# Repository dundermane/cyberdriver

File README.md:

CyberDriver
===========

Driver for the Kopin Cyberdisplay 320m

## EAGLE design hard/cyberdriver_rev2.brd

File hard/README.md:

Hardware
=========

<h2>Eagle Version: <i>v6.5.0</i></h2>

<h3>all parts must be saved in the cyberdriver.lbr library</h3>
<h4>open cyberdriver.lbr and try [right-click -> Copy To Library] in the control panel</h4>
<h4><i>extra steps suck. but so does losing all of your work when a library changes</i></h4>

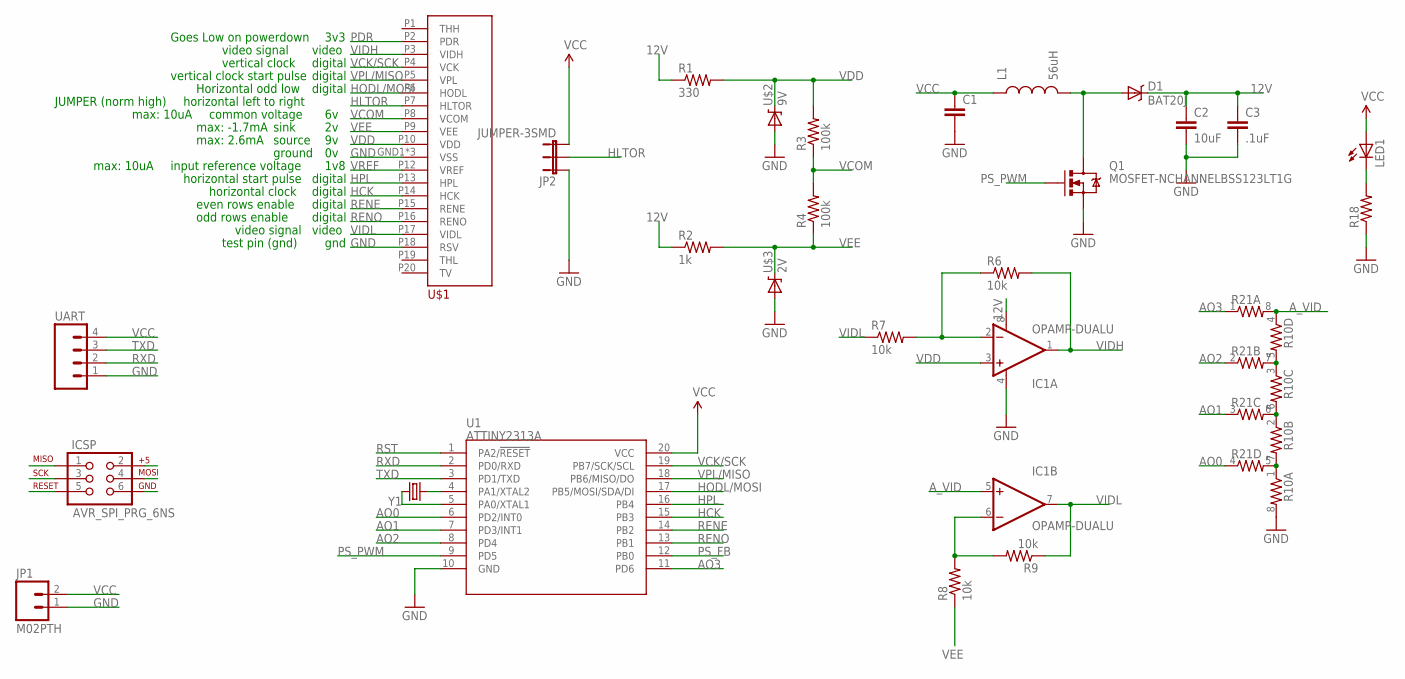
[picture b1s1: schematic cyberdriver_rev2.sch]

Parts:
C1: CAP1206; 1206
C2: 10uF; 1210
C3: .1uF; 0603-CAP
D1: BAT20J; SOD-323
IC1: OPAMP-DUALU; SO08
ICSP: AVR_SPI_PRG_6NS; 2X3-NS
JP1: M02PTH; 1X02
JP2: JUMPER-3SMD; SJ_3
L1: 56uH; SDR0403
LED1: LED1206; LED-1206
Q1: MOSFET-NCHANNELBSS123LT1G; SOT23
R1: 330; 0603-RES
R2: 1k; 0603-RES
R3, R4: 100k; 0603-RES
R6, R7, R8, R9: 10k; 0603-RES
R10, R21: RESISTOR-ARRAY0603-ARV; 0603-ARV
R18: RESISTOR0805-RES; 0805
U1: ATTINY2313A; SOP20W
U$1: CYBERDISPLAY-CONN; MOLEX-54550-2071
U$2: 9V; SOD-323
U$3: 2V; SOD-323
UART: M041.27MM; 1X04-1.27MM
Y1: CRYSTAL5X3; CRYSTAL-SMD-5X3

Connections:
12V: C2.1, C3.1, D1.C, IC1.8 (V+), R1.1, R2.1
AO0: R21.4 (1), U1.6 (PD2/INT0)
AO1: R21.3 (1), U1.7 (PD3/INT1)
AO2: R21.2 (1), U1.8 (PD4)
AO3: R21.1, U1.11 (PD6)
A_VID: IC1.5 (+IN), R10.4 (1), R21.8 (2)
GND: C1.2, C2.2, C3.2, IC1.4 (V-), ICSP.6, JP1.1, JP2.1, Q1.2 (S), R10.8 (2), R18.1, U1.10 (GND), U$1.GND1 (VSS), U$1.GND20 (VSS), U$1.P11 (VSS), U$1.P18 (RSV), U$2.A, U$3.A, UART.1
HCK: U1.15 (PB3), U$1.P14 (HCK)
HLTOR: JP2.2, U$1.P7 (HLTOR)
HODL/MOSI: ICSP.4, U1.17 (PB5/MOSI/SDA/DI), U$1.P6 (HODL)
HPL: U1.16 (PB4), U$1.P13 (HPL)
unnamed: U1.5 (PA0/XTAL1), Y1.3 (2)
unnamed: U1.4 (PA1/XTAL2), Y1.1
unnamed: LED1.C, R18.2
unnamed: D1.A, L1.P$2 (2), Q1.3 (D)
unnamed: IC1.2 (-IN), R6.1, R7.2
unnamed: R10.3 (1), R10.5 (2), R21.7 (2)
unnamed: IC1.6 (-IN), R8.2, R9.2
unnamed: R10.2 (1), R10.6 (2), R21.6 (2)
unnamed: R10.1, R10.7 (2), R21.5 (2)
PDR: U$1.P2 (PDR)
PS_FB: U1.12 (PB0)
PS_PWM: Q1.1 (G), U1.9 (PD5)
RENE: U1.14 (PB2), U$1.P15 (RENE)
RENO: U1.13 (PB1), U$1.P16 (RENO)
RST: ICSP.5, U1.1 (PA2/!RESET)
RXD: U1.2 (PD0/RXD), UART.2
TXD: U1.3 (PD1/TXD), UART.3
VCC: C1.1, ICSP.2, JP1.2, JP2.3, L1.P$1 (1), LED1.A, U1.20 (VCC), UART.4
VCK/SCK: ICSP.3, U1.19 (PB7/SCK/SCL), U$1.P4 (VCK)
VCOM: R3.1, R4.2, U$1.P8 (VCOM)
VDD: IC1.3 (+IN), R1.2, R3.2, U$1.P10 (VDD), U$2.C
VEE: R2.2, R4.1, R8.1, U$1.P9 (VEE), U$3.C
VIDH: IC1.1 (OUT), R6.2, U$1.P3 (VIDH)
VIDL: IC1.7 (OUT), R7.1, R9.1, U$1.P17 (VIDL)
VPL/MISO: ICSP.1, U1.18 (PB6/MISO/DO), U$1.P5 (VPL)
VREF: U$1.P12 (VREF)

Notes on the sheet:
Goes Low on powerdown
video signal
vertical clock
vertical clock start pulse
Horizontal odd low
horizontal left to right
common voltage
sink
source
ground
input reference voltage
horizontal start pulse
horizontal clock
even rows enable
odd rows enable
test pin (gnd)
digital
video
gnd
3v3
1v8
JUMPER (norm high)
max: 2.6mA
max: -1.7mA
max: 10uA

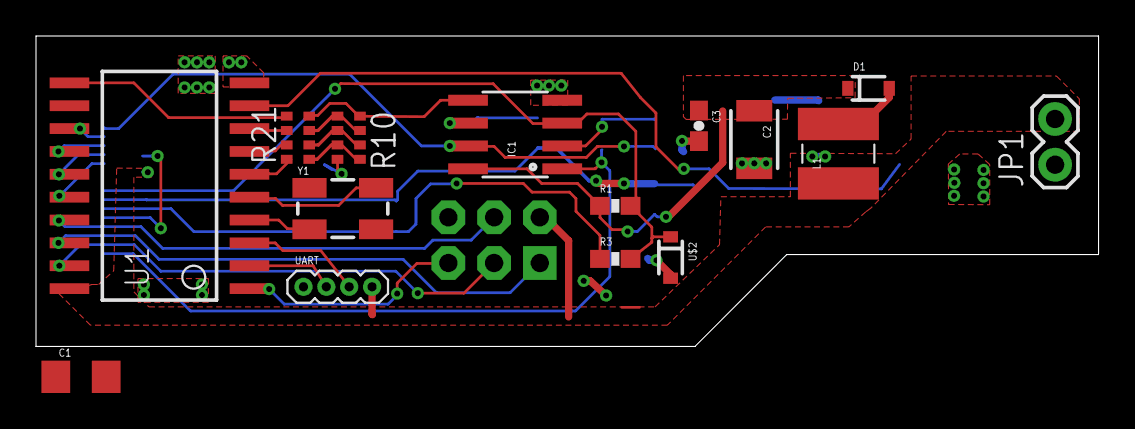
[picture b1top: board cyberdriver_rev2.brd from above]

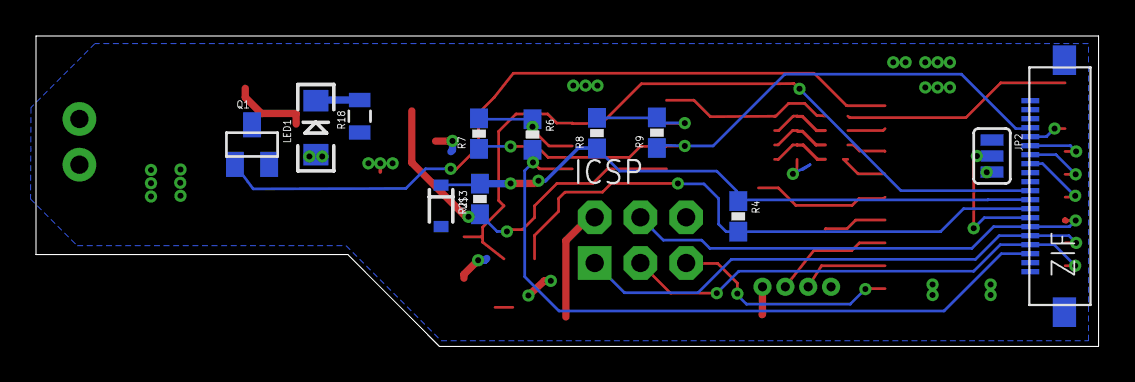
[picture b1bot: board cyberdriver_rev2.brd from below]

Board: 2 copper layers, 59.0 x 17.2 mm, 28 parts (13 on the bottom side), 34 nets.

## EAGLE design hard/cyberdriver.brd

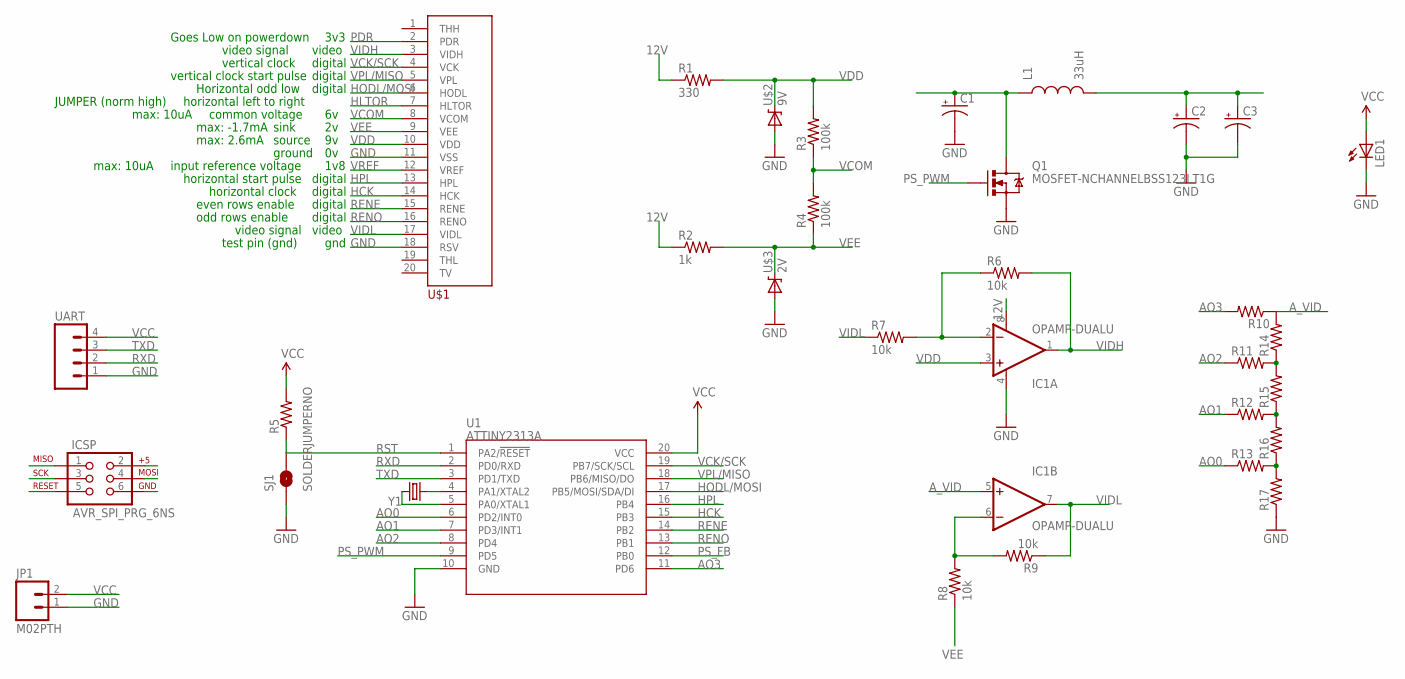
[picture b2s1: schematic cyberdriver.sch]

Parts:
C1, C2: CAP_POLC; PANASONIC_C
C3: CAP_POL1206; EIA3216
IC1: OPAMP-DUALU; SO08@1
ICSP: AVR_SPI_PRG_6NS; 2X3-NS
JP1: M02PTH; 1X02
L1: 33uH; SRN6045
LED1: LED1206; LED-1206
Q1: MOSFET-NCHANNELBSS123LT1G; SOT23
R1: 330; 0603-RES
R2: 1k; 0603-RES
R3, R4: 100k; 0805
R5, R10, R11, R12, R13, R14, R15, R16, R17: RESISTOR0805-RES; 0805
R6, R7, R8, R9: 10k; 0805
SJ1: SOLDERJUMPERNO; SJ_2S-NO
U1: ATTINY2313A; SOP20W
U$1: CYBERDISPLAY-CONN; MOLEX-54550-2071
U$2: 9V; SOD-323
U$3: 2V; SOD-323
UART: M04PTH; 1X04
Y1: CRYSTAL5X3; CRYSTAL-SMD-5X3

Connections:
12V: C2.+, C3.A (+), IC1.8 (V+), L1.2, R1.1, R2.1
AO0: R13.1, U1.6 (PD2/INT0)
AO1: R12.1, U1.7 (PD3/INT1)
AO2: R11.1, U1.8 (PD4)
AO3: R10.2, U1.11 (PD6)
A_VID: IC1.5 (+IN), R10.1, R14.2
GND: C1.-, C2.-, C3.C (-), IC1.4 (V-), ICSP.6, JP1.1, LED1.C, Q1.2 (S), R17.1, SJ1.1, U1.10 (GND), U$1.11 (VSS), U$1.18 (RSV), U$2.A, U$3.A, UART.1
HCK: U1.15 (PB3), U$1.14 (HCK)
HLTOR: U$1.7 (HLTOR)
HODL/MOSI: ICSP.4, U1.17 (PB5/MOSI/SDA/DI), U$1.6 (HODL)
HPL: U1.16 (PB4), U$1.13 (HPL)
unnamed: U1.5 (PA0/XTAL1), Y1.3 (2)
unnamed: U1.4 (PA1/XTAL2), Y1.1
unnamed: C1.+, L1.1, Q1.3 (D)
unnamed: IC1.2 (-IN), R6.1, R7.2
unnamed: R11.2, R14.1, R15.2
unnamed: IC1.6 (-IN), R8.2, R9.2
unnamed: R12.2, R15.1, R16.2
unnamed: R13.2, R16.1, R17.2
PDR: U$1.2 (PDR)
PS_FB: U1.12 (PB0)
PS_PWM: Q1.1 (G), U1.9 (PD5)
RENE: U1.14 (PB2), U$1.15 (RENE)
RENO: U1.13 (PB1), U$1.16 (RENO)
RST: ICSP.5, R5.1, SJ1.2, U1.1 (PA2/!RESET)
RXD: U1.2 (PD0/RXD), UART.2
TXD: U1.3 (PD1/TXD), UART.3
VCC: ICSP.2, JP1.2, LED1.A, R5.2, U1.20 (VCC), UART.4
VCK/SCK: ICSP.3, U1.19 (PB7/SCK/SCL), U$1.4 (VCK)
VCOM: R3.1, R4.2, U$1.8 (VCOM)
VDD: IC1.3 (+IN), R1.2, R3.2, U$1.10 (VDD), U$2.C
VEE: R2.2, R4.1, R8.1, U$1.9 (VEE), U$3.C
VIDH: IC1.1 (OUT), R6.2, U$1.3 (VIDH)
VIDL: IC1.7 (OUT), R7.1, R9.1, U$1.17 (VIDL)
VPL/MISO: ICSP.1, U1.18 (PB6/MISO/DO), U$1.5 (VPL)
VREF: U$1.12 (VREF)

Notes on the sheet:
Goes Low on powerdown
video signal
vertical clock
vertical clock start pulse
Horizontal odd low
horizontal left to right
common voltage
sink
source
ground
input reference voltage
horizontal start pulse
horizontal clock
even rows enable
odd rows enable
test pin (gnd)
digital
video
gnd
3v3
1v8
JUMPER (norm high)
max: 2.6mA
max: -1.7mA
max: 10uA

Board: 2 copper layers, 33 parts (1 on the bottom side), 32 nets, no tracks yet.

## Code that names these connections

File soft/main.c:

/*
Lets blink the ps_pwm pin


logical 0 :  PORTB &= ~(1<<PB0);
logical 1 :  PORTB |= (1<<PB0);

*/

#include <avr/io.h>

#define d_ps_pwm PD5
//PD5 is OC0B
#define d_a0 PD2
#define d_a1 PD3
#define d_a2 PD4
#define d_a3 PD6

#define b_HODL PB5
#define b_HPL PB4
#define b_HCK PB3
#define b_VCK PB7
#define b_VPL PB6
#define b_RENE PB2
#define b_RENO PB1

void delay_ms(uint8_t ms) {
	uint16_t delay_count = 16000 / 64;
	volatile uint16_t i;
	
	while (ms != 0) {
		for (i=0; i != delay_count; i++);
		ms--;
	}
}

void a_vid(uint8_t grey) {
	

	PORTD &= ~(1<<d_a0);
	PORTD |= (grey % 2 << d_a0);
	PORTD &= ~(1<<d_a1);
	PORTD |= ((grey >> 1) % 2 << d_a1);
	PORTD &= ~(1<<d_a2);
	PORTD |= ((grey >> 2) % 2 << d_a2);
	PORTD &= ~(1<<d_a3);
	PORTD |= ((grey >> 3) % 2 << d_a3);
	
}

void dumpOnScreen(uint8_t rows, uint8_t cols, uint8_t *img){

//img is a pointer for the first item in array


}

int main(void) {
	
	DDRD = 0xFF;  //All digital outs to 0
	DDRB = 0xFF;
	PORTD = 0x00;
	PORTB = 0x00;


/**********
 PWM INIT
**********/
	TCCR0A = 0x00; //init tccr0a. probs dont need to do that tho
	OCR0A = 0x0F;
    OCR0B  = 0x03;                          // initial PWM pulse width
    DDRD   |= (1 << d_ps_pwm);                   // PWM output on PD5
    TCCR0A |= (1 << WGM00) | (1 << WGM01); // fast PWM with orc0a as top
    TCCR0B |= (1 << WGM02); //Because WGM2 is in a dif register. DUMB
    
    TCCR0A |= (1 << COM0B1); //OC0B duty low on compare match
    TCCR0B |= (1 << CS00);   //Clock Divider for pwm 

/************
 DISPLAY INIT
************/
    
	uint8_t image[40] = {0x3, 0x3, 0x3, 0x3, 0x3, 0x3,
					   0x3, 0x3, 0x3, 0x3, 0x3, 0x3,
					   0x3, 0x3, 0x3, 0x3, 0x3, 0x3,
					   0x3, 0x3, 0x3, 0x3, 0x3, 0x3,
					   0x3, 0x3, 0x3, 0x3, 0x3, 0x3,
					   0x3, 0x3, 0x3, 0x3, 0x3, 0x3};
	
    uint8_t *img;

/***********
 Main Loop
***********/
	for(;;) {
	
	
		a_vid(0);
		delay_ms(2000);
		a_vid(15);
		delay_ms(2000);

		dumpOnScreen(6,6,&img[0]);		
	}

	return 0;
}

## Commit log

2014-04-24 added resources
2014-04-24 added blank hardware files
2014-04-24 Hardware Readme
2014-04-24 added the flex connector to library
2014-04-25 updated library. started schematic
2014-04-25 Display Power Regs Added
2014-04-25 Changes to Schematic and New Board
2014-09-02 Firmware started (ps working, adc sort of) hardware rev2 started
2014-09-05 matt commit

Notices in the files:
parts and their libraries:
SparkFun-Passives: Licensing: Creative Commons ShareAlike 4.0 International - https://creativecommons.org/licenses/by-sa/4.0
